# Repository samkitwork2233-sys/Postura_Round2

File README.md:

#  Postura

> **Smart Wearable Posture Monitoring & Ergonomic Habit Correction System**

Postura is a wearable posture-monitoring system designed to help users build and maintain healthy spinal habits. It pairs custom physical hardware with a modern Flutter mobile application over Bluetooth Low Energy (BLE), offering **live posture angle tracking**, **instant on-body haptic feedback**, and **detailed session analytics**.

---

## Overview

Poor posture during extended desk work, gaming, or studying contributes to spinal strain, chronic neck/back pain, and fatigue.

**Postura provides continuous ergonomic assistance:**
1. **Dynamic Baseline Calibration**: Calibrates to your natural upright posture at the tap of a button when starting a session.
2. **Continuous Real-Time Tracking**: Continuously monitors angular tilt and deviation from your calibrated baseline.
3. **Instant Dual Feedback**: Triggers both on-body haptic vibration and mobile UI alerts the moment you breach ergonomic limits.
4. **Session Analytics & Scoring**: Evaluates posture consistency, logs slouch frequency, calculates a posture health score, and archives sessions locally.

---

## How It Works

```text
       +-------------------------------------------------------------+
       |                       WEARABLE DEVICE                       |
       |  [ MPU6050 IMU ] -> [ ESP32 Processing ] -> [ Vibration ]   |
       +------------------------------+------------------------------+
                                      |
                                      | BLE Stream (Angle, Deviation)
                                      v
       +-------------------------------------------------------------+
       |                      POSTURA FLUTTER APP                    |
       |                                                             |
       |  1. BLE Connection & Device Discovery                       |
       |  2. Real-Time Gauge & Deviation Visualization               |
       |  3. Active Session Monitoring & Posture Scoring Engine      |
       |  4. Local Session Storage & Historical Insights             |
       +-------------------------------------------------------------+
```

### Complete User Flow
1. **Pair & Connect**: Launch the app and connect to your Postura wearable via Bluetooth Low Energy.
2. **Start Session**: Sit upright and tap **Start Session**—the app automatically calibrates your baseline reference angle and begins tracking.
3. **Live Monitoring**: Work or study comfortably while the app tracks real-time tilt angle, deviation, and session time.
4. **Active Alerts**: If you slouch beyond your custom threshold (e.g. >15°), the wearable vibrates immediately and the app UI switches to alert mode.
5. **Save & Review**: Conclude your session to save the duration, slouch count, and computed posture score into your local history and analytics dashboard.

---

## Hardware Architecture

The Postura wearable is built around an integrated embedded architecture that performs low-latency sensor acquisition and BLE communication.

```text
   +---------------+
   | Lithium LiPo  |
   |    Battery    |
   +-------+-------+
           |
           v
   +---------------+       I2C       +---------------+
   | Power / TP4056| --------------> | MPU6050 6-DoF |
   | Charging Board|                 |  IMU Sensor   |
   +---------------+                 +-------+-------+
           |                                 |
           | 3.3V Power                      | Raw Accelerometer & Gyro
           v                                 v
   +-------------------------------------------------+
   |                 ESP32 Microcontroller           |
   |  - Complementary filter & angle calculation     |
   |  - BLE GATT server (Postura telemetry service)  |
   |  - PWM motor driver control                     |
   +-----------------------+-------------------------+
                           |
            +--------------+--------------+
            |                             |
            v                             v
   +------------------+         +-------------------+
   | Vibration Motor  |         | Status Indicator  |
   | (Haptic Feedback)|         |       LEDs        |
   +------------------+         +-------------------+
```

### Key Hardware Components
| Component | Function |
| :--- | :--- |
| **ESP32 MCU** | Dual-core microcontroller managing sensor polling, angle filtering, BLE GATT server, and motor control. |
| **MPU6050 IMU** | 6-axis inertial measurement unit (3-axis gyroscope + 3-axis accelerometer) capturing spinal tilt and orientation. |
| **Vibration Motor** | Coin-type ERM motor providing discreet on-body haptic feedback during bad posture. |
| **Power & Battery** | Rechargeable LiPo battery with dedicated TP4056 micro-USB / USB-C charging circuitry. |
| **Status LEDs** | Board-level indicators for power, BLE connection status, and charging state. |
| **Custom PCB** | Designed using KiCad for compact wearable form-factor (`hardware/pcb/`). |

### BLE Communication Protocol
- **Device Advertised Name**: `POSTURA_V3`
- **Service UUID**: `12345678-1234-1234-1234-1234567890ab`
- **Characteristic UUID**: `abcd1234-5678-1234-5678-abcdef123456`
- **Data Stream Format**: Transmits live ASCII strings in the format `<angle>,<deviation>` (e.g. `62.5,2.1`).
- **Downlink Commands**:
  - `THRESHOLD:<val>` - Updates the on-device posture slouch tolerance (e.g., `THRESHOLD:15`).
  - `BASE:<val>` - Sends calibrated base reference angle to firmware (e.g., `BASE:60`).

---

## Software Architecture (Flutter Companion App)

The mobile companion application is built with **Flutter & Dart**, focusing on smooth 60fps telemetry rendering, intuitive ergonomic feedback, and offline-first data persistence.

```text
lib/
├── app/
│   ├── history/              # Session history view & detail screens
│   ├── home/                 # Main posture dashboard page
│   ├── insights/             # Weekly/Monthly posture analytics & trends
│   ├── router/               # GoRouter indexed stack navigation
│   └── settings/             # Threshold, theme, & vibration configuration
├── modules/
│   ├── posture/
│   │   ├── actions/          # BLE permissions & connection action handlers
│   │   ├── core/             # Riverpod PostureNotifier & PostureState
│   │   └── services/         # BleService (flutter_blue_plus)
│   └── storage/
│       ├── core/             # History & Settings Riverpod providers
│       ├── models/           # Hive SessionModel entity
│       └── services/         # Hive HistoryService & SharedPreferences
├── shared/
│   ├── components/
│   │   ├── templates/        # Page layout templates & shells
│   │   └── ui/               # GlassCard, PostureGauge, AnimatedButtons
│   └── constants/            # Design tokens, AppColors, AppTheme
└── main.dart                 # App bootstrap & Hive/Settings initialization
```

### Key Software Highlights
- **State Management (Riverpod)**: Unidirectional data flow handling live BLE streams, timer ticks, and posture score computation.
- **Local-First Storage (Hive & SharedPreferences)**: Fast, zero-lag local database storing all previous sessions with zero cloud dependency.
- **Modern Glassmorphism UI**: Polished Material 3 design with dynamic Light/Dark mode support, custom posture radial indicator gauge, and responsive widgets.
- **Data Analytics & Insights**: Interactive chart rendering (`fl_chart`) tracking average posture score, slouch frequency, and total active monitoring time.
- **Granular Customization**: Adjustable slouch angle threshold (5° - 30°) and vibration duration.

---

## Scoring & Posture Evaluation Algorithm

Postura evaluates session quality using both time-in-posture and penalty deductions:

$$\text{Time Score} = \left( \frac{\text{Good Posture Seconds}}{\text{Total Session Seconds}} \right) \times 100$$

$$\text{Final Score} = \operatorname{clamp}\Big( \text{Time Score} - (\text{Slouch Count} \times 2.0), \; 0, \; 100 \Big)$$

- **Good Posture**: Measured deviation is within the configured threshold ($\Delta \le \theta$).
- **Slouch Event**: Triggered when deviation exceeds threshold ($\Delta > \theta$), incrementing the slouch counter and activating alerts.

---

## Getting Started

### Prerequisites
- [Flutter SDK](https://flutter.dev/docs/get-started/install) (v3.10+ / Dart 3+)
- Android Studio / VS Code with Flutter extensions
- Android device or emulator with Bluetooth 4.2+ (BLE) support

### Installation & Run

1. **Clone the repository**:
   ```bash
   git clone https://github.com/your-username/Postura_Round2.git
   cd Postura_Round2
   ```

2. **Install Flutter dependencies**:
   ```bash
   flutter pub get
   ```

3. **Generate Hive TypeAdapters** (if modifying models):
   ```bash
   dart run build_runner build --delete-conflicting-outputs
   ```

4. **Run the application**:
   ```bash
   flutter run
   ```

---

## Hardware Design Files

All hardware schematics, PCB layouts, and fabrication assets are provided in the [`hardware/`](file:///c:/Users/Prashant%20Bhandari/Documents/Flutter%20Projects/Postura_Round2/hardware) directory:
- [`hardware/schematic/`](file:///c:/Users/Prashant%20Bhandari/Documents/Flutter%20Projects/Postura_Round2/hardware/schematic) — KiCad schematic files (`.kicad_sch`)
- [`hardware/pcb/`](file:///c:/Users/Prashant%20Bhandari/Documents/Flutter%20Projects/Postura_Round2/hardware/pcb) — KiCad PCB layout and routing files (`.kicad_pcb`)
- [`hardware/images/`](file:///c:/Users/Prashant%20Bhandari/Documents/Flutter%20Projects/Postura_Round2/hardware/images) — Rendered board layouts and circuit diagrams

---

## License

This project is licensed under the MIT License — see the [LICENSE](LICENSE) file for details.

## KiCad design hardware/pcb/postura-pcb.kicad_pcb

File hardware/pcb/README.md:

# Postura PCB Design

This folder contains the KiCad PCB layout for the Postura wearable hardware.

The PCB design integrates the major electronic components required for the wearable posture-monitoring system and provides the physical board layout corresponding to the hardware schematic.

## PCB Design Scope

The PCB design covers:

- Component placement
- Electrical connectivity
- Power distribution
- Sensor integration
- ESP32 integration
- Feedback circuitry
- PCB routing
- Compact wearable form factor

## Design File

The main PCB design file is:

`postura-pcb.kicad_pcb`

This file can be opened and further edited using KiCad.

## Hardware Integration

The PCB is designed to connect the sensing, processing, communication, power, and feedback sections of the Postura wearable into an integrated hardware platform.

## Development Status

The PCB represents the current hardware development of the Postura prototype.

Further optimization for mass manufacturing, enclosure integration, production testing, and design-for-manufacturing can be performed in future iterations.

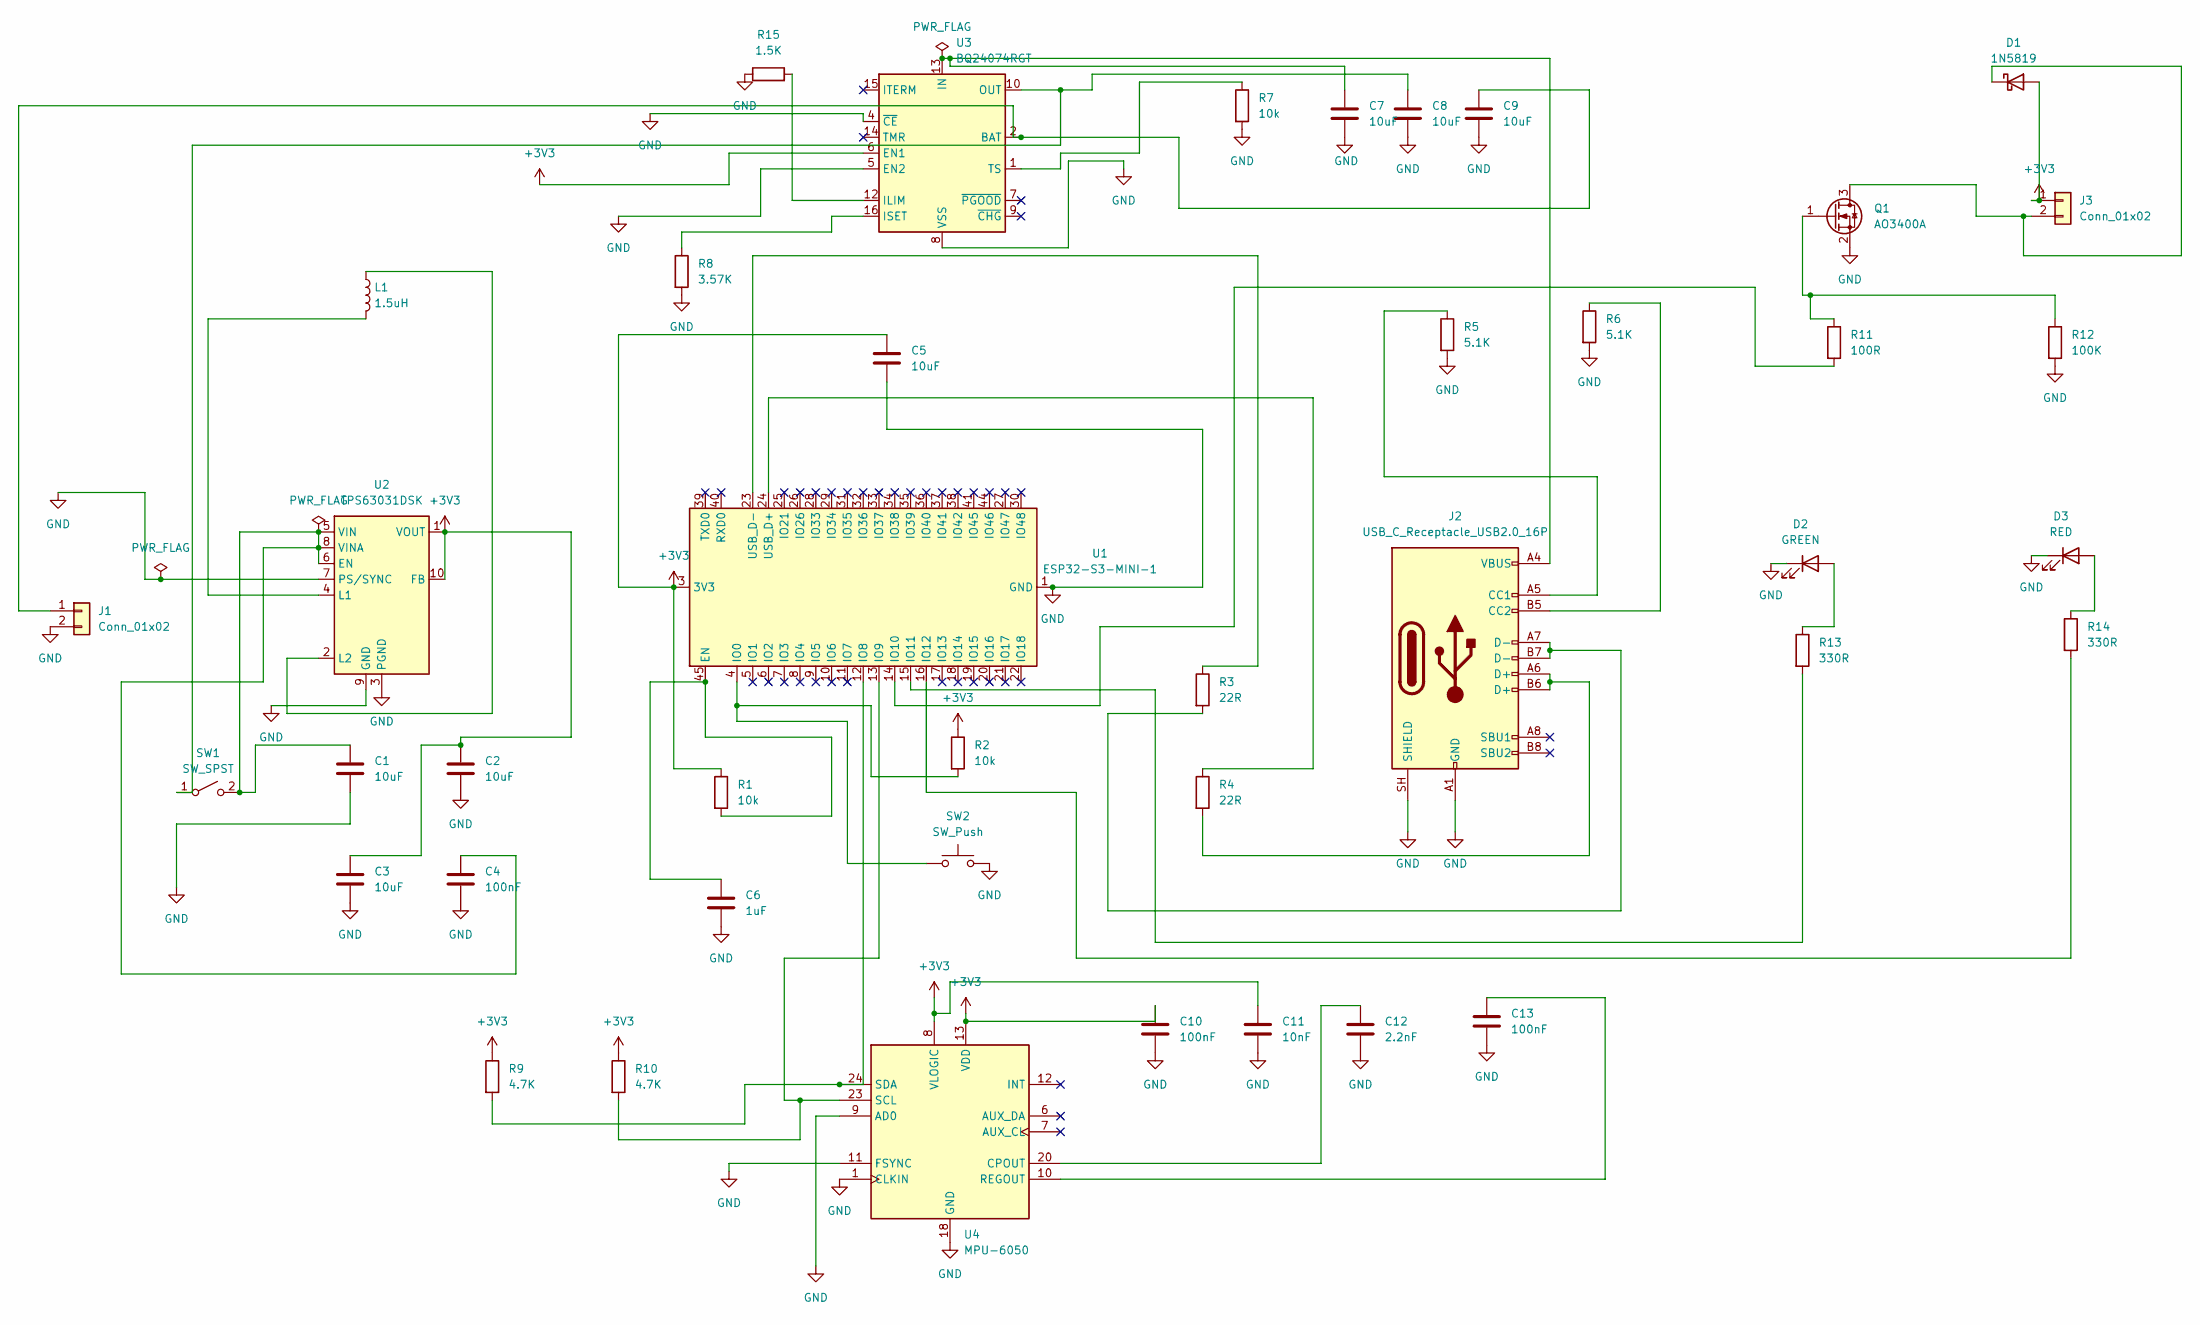
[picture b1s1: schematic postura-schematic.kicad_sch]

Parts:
C1, C2, C3, C5, C7, C8, C9: 10uF; C_0805_2012Metric
C4, C10, C13: 100nF; C_0805_2012Metric
C6: 1uF; C_0805_2012Metric
C11: 10nF; C_0805_2012Metric
C12: 2.2nF; C_0805_2012Metric
D1: 1N5819; D_SOD-123
D2: GREEN; LED_0805_2012Metric
D3: RED; LED_0805_2012Metric
J1, J3: Conn_01x02; JST_PH_S2B-PH-K_1x02_P2.00mm_Horizontal
J2: USB_C_Receptacle_USB2.0_16P; USB_C_Receptacle_GCT_USB4105-xx-A_16P_TopMnt_Horizontal
L1: 1.5uH; L_Coilcraft_LPS3010
Q1: AO3400A; SOT-23
R1, R2, R7: 10k; R_0805_2012Metric
R3, R4: 22R; R_0805_2012Metric
R5, R6: 5.1K; R_0805_2012Metric
R8: 3.57K; R_0805_2012Metric
R9, R10: 4.7K; R_0805_2012Metric
R11: 100R; R_0805_2012Metric
R12: 100K; R_0805_2012Metric
R13, R14: 330R; R_0805_2012Metric
R15: 1.5K; R_0805_2012Metric
SW1: SW_SPST; SW_Slide_SPDT_Straight_CK_OS102011MS2Q
SW2: SW_Push; SW_Push_1P1T_NO_CK_KMR2
U1: ESP32-S3-MINI-1; ESP32-S2-MINI-1
U2: TPS63031DSK; WSON-10-1EP_2.5x2.5mm_P0.5mm_EP1.2x2mm
U3: BQ24074RGT; VQFN-16-1EP_3x3mm_P0.5mm_EP1.6x1.6mm
U4: MPU-6050; InvenSense_QFN-24_4x4mm_P0.5mm

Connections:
+3V3: C2.1, C3.1, C5.1, C10.1, C11.1, D1.2 (A), J3.1, R1.1, R2.1, R9.1, R10.1, U1.3 (3V3), U2.1 (VOUT), U2.10 (FB), U3.6 (EN1), U4.8 (VLOGIC), U4.13 (VDD)
GND: C1.2, C2.2, C3.2, C4.2, C5.2, C6.2, C7.2, C8.2, C9.2, C10.2, C11.2, C12.2, C13.2, D2.1 (K), D3.1 (K), J1.2, J2.A1 (GND), J2.A12 (GND), J2.B1 (GND), J2.B12 (GND), J2.SH (SHIELD), Q1.2 (S), R5.2, R6.2, R7.2, R8.2, R12.2, R15.1, SW2.2, U1.1 (GND), U1.2 (GND), U1.42 (GND), U1.43 (GND), U1.46 (GND), U1.47 (GND), U1.48 (GND), U1.49 (GND), U1.50 (GND), U1.51 (GND), U1.52 (GND), U1.53 (GND), U1.54 (GND), U1.55 (GND), U1.56 (GND), U1.57 (GND), U1.58 (GND), U1.59 (GND), U1.60 (GND), U1.61 (GND), U1.62 (GND), U1.63 (GND), U1.64 (GND), U1.65 (GND), U2.3 (PGND), U2.7 (PS/SYNC), U2.9 (GND), U2.11 (PGND), U3.4 (~CE), U3.5 (EN2), U3.8 (VSS), U3.17 (VSS), U4.1 (CLKIN), U4.9 (AD0), U4.11 (FSYNC), U4.18 (GND)
unnamed: D1.1 (K), J3.2, Q1.3 (D)
unnamed: D2.2 (A), R13.1
unnamed: D3.2 (A), R14.1
unnamed: C9.1, J1.1, U3.2 (BAT), U3.3 (BAT)
unnamed: J2.A5 (CC1), R5.1
unnamed: J2.B5 (CC2), R6.1
unnamed: J2.A6 (D+), J2.B6 (D+), R4.2
unnamed: J2.A7 (D-), J2.B7 (D-), R3.2
unnamed: Q1.1 (G), R11.1, R12.1
unnamed: C8.1, SW1.1 (A), U3.10 (OUT), U3.11 (OUT)
unnamed: C1.1, C4.1, SW1.2 (B), U2.5 (VIN), U2.6 (EN), U2.8 (VINA)
unnamed: C6.1, R1.2, U1.45 (EN)
unnamed: R2.2, SW2.1, U1.4 (IO0)
unnamed: R9.2, U1.12 (IO8), U4.24 (SDA)
unnamed: R10.2, U1.13 (IO9), U4.23 (SCL)
unnamed: R11.2, U1.14 (IO10)
unnamed: R13.2, U1.15 (IO11)
unnamed: R14.2, U1.16 (IO12)
unnamed: R4.1, U1.24 (USB_D+)
unnamed: R3.1, U1.23 (USB_D-)
unnamed: L1.2, U2.4 (L1)
unnamed: L1.1, U2.2 (L2)
unnamed: R15.2, U3.12 (ILIM)
unnamed: C7.1, J2.A4 (VBUS), J2.A9 (VBUS), J2.B4 (VBUS), J2.B9 (VBUS), U3.13 (IN)
unnamed: R8.1, U3.16 (ISET)
unnamed: R7.1, U3.1 (TS)
unnamed: C12.1, U4.20 (CPOUT)
unnamed: C13.1, U4.10 (REGOUT)

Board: 2 copper layers, 42 parts (0 on the bottom side), 30 nets, no tracks yet.

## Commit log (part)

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2026-04-02 postura init
2026-04-02 history and real time score
2026-04-03 sync with hardware and filtering
2026-04-03 sensitivty preservance
2026-04-03 sensitivity fix hard
